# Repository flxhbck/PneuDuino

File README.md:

# PneuDuino

Pneuduino is a toolkit for controlling air flow and pressure to design robots that are soft, furniture that is adaptive, clothing that is intelligent, art pieces that are breathing, and many more things.

Disclaimer:
This toolkit is currently designed for workshops that we give. We are working on a more stable version for personal use. In the meantime, you are welcome to use what you find here - but be aware that is a work in progress.

For more information visit http://pneuduino.org/toolkit/

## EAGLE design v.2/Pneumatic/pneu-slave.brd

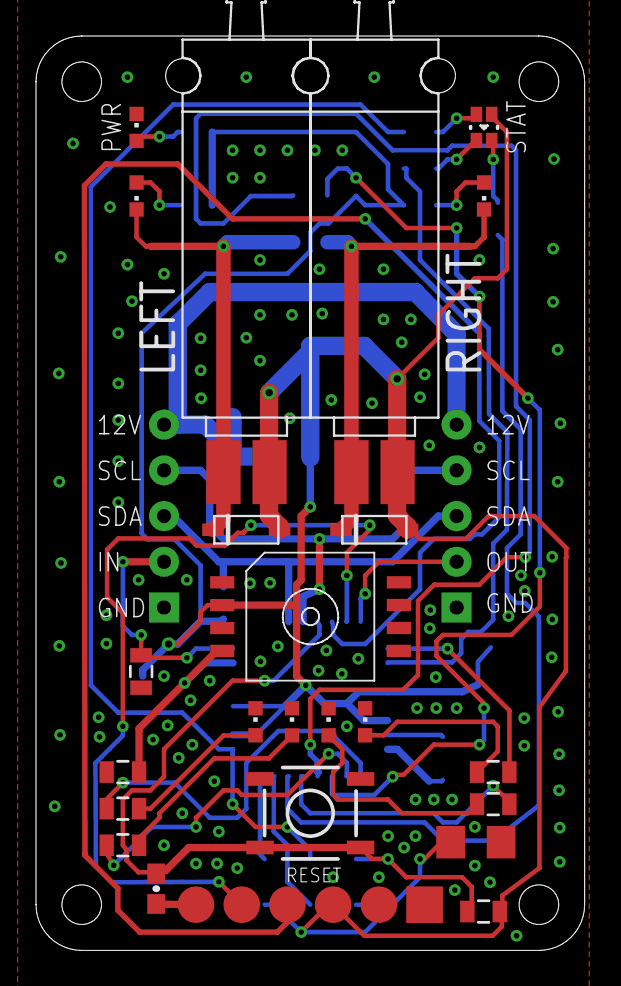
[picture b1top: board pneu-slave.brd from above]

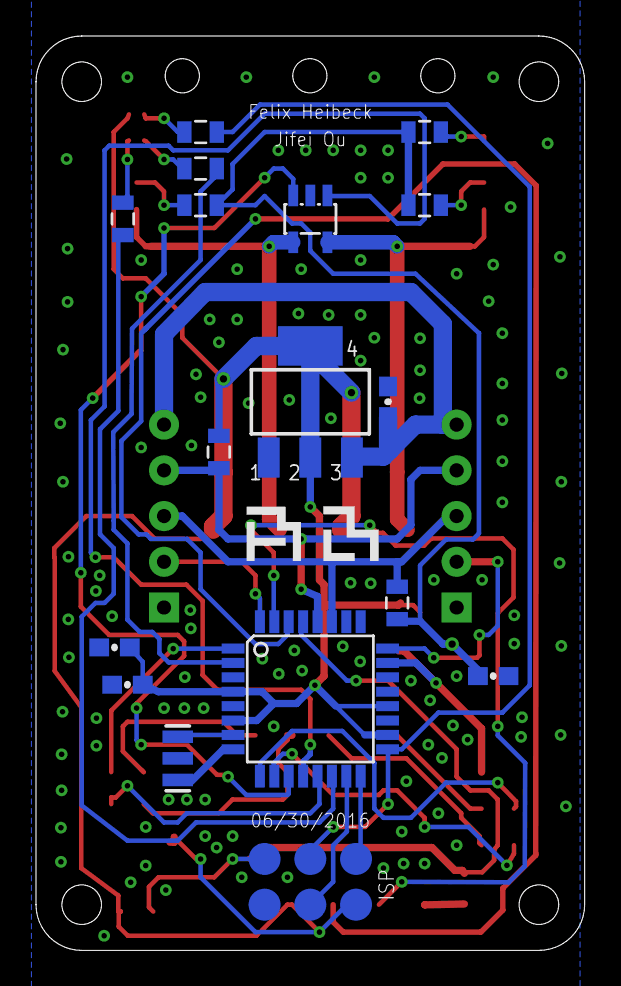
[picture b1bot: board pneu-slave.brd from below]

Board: 2 copper layers, 30.5 x 50.8 mm, 42 parts (17 on the bottom side), 37 nets.

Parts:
C1, C2, C5, C8, C10: 0.1uF; 0603-CAP
C4: 22uF; 1206
C7: 470pF; 0805
D1, D2: SOD-123
LED_PR1, LED_PR2, LED_PR3, LED_PR4: WHITE; CHIPLED_0603
LED_PWR: RED; CHIPLED_0603
LED_STATUS: LTST-C19FD1WT; LTST
LED_V1, LED_V2: WHITE; CHIPLED_0603
Q1: 16Mhz; RESONATOR-SMD
R1, R2, R4, R7, R8, R9, R10, R11, R12, R13: 1k; 0805
R3: 10K; 0805
R5, R6: 4.7k; 0805
R14: 10k; 0805
S1: TAC_SWITCHSMD; TACTILE-SWITCH-SMD
U0: ATMEGA328; TQFP32-08
U1: NCP1117-5; LINEAR_SOT223
U2: MPXHZ6400
U3: QS5K2; SOT23-5L
U$10: ISP_POGO; POGO_ISP
U$11: S070V-2VALVE; S070C-2
U$12: FTDI_POGO
U$23, U$24: 1X05; 1X05_TIGHT

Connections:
+5V: C2.1, C4.1, C8.1, C10.1, D1.C, D2.C, LED_STATUS.+, R2.2, R3.1, R5.1, R6.2, R8.2, R11.2, U0.4, U0.6, U0.18, U0.20, U1.2, U1.4, U2.2, U$10.2, U$11.1-2, U$11.2-2, U$12.4
A0/PRESSURE: C7.2, U0.23, U2.4
D2/OUT: U0.32, U$23.P$4
D3: R1.2, U0.1
D4: R9.2, U0.2
D5: R7.2, U0.9
D6: R4.2, U0.10
D7: U0.11, U3.3
D8: U0.12, U3.1
D9: R10.2, U0.13
D10: R12.2, U0.14
DTR: C5.2, U$12.1
GND: C1.2, C2.2, C4.2, C7.1, C8.2, C10.2, LED_PR1.C, LED_PR2.C, LED_PR3.C, LED_PR4.C, LED_PWR.C, Q1.2, R14.1, S1.1, S1.2, U0.3, U0.5, U0.21, U1.1, U2.3, U3.2, U$10.6, U$12.5, U$12.6, U$23.P$5, U$24.P$5
IN_PORT: R14.2, U0.24, U$24.P$4
M1_VGND: D1.A, LED_V2.C, U3.4, U$11.2-1
M2_VGND: D2.A, LED_V1.C, U3.5, U$11.1-1
MISO: U0.16, U$10.1
MOSI: U0.15, U$10.4
unnamed: LED_PR2.A, R4.1
unnamed: LED_PR1.A, R7.1
unnamed: Q1.1, U0.8
unnamed: LED_PR4.A, R1.1
unnamed: LED_V2.A, R2.1
unnamed: LED_V1.A, R8.1
unnamed: Q1.3, U0.7
unnamed: LED_PR3.A, R10.1
unnamed: LED_PWR.A, R11.1
unnamed: LED_STATUS.R, R9.1
unnamed: LED_STATUS.G, R12.1
unnamed: LED_STATUS.B, R13.1
RESET: C5.1, R3.2, S1.3, S1.4, U0.29, U$10.5
RX: U0.30, U$12.3
SCK: R13.2, U0.17, U$10.3
SCL: R6.1, U0.28, U$23.P$3, U$24.P$3
SDA: R5.2, U0.27, U$23.P$2, U$24.P$2
TX: U0.31, U$12.2
VIN: C1.1, U1.3, U$23.P$1, U$24.P$1

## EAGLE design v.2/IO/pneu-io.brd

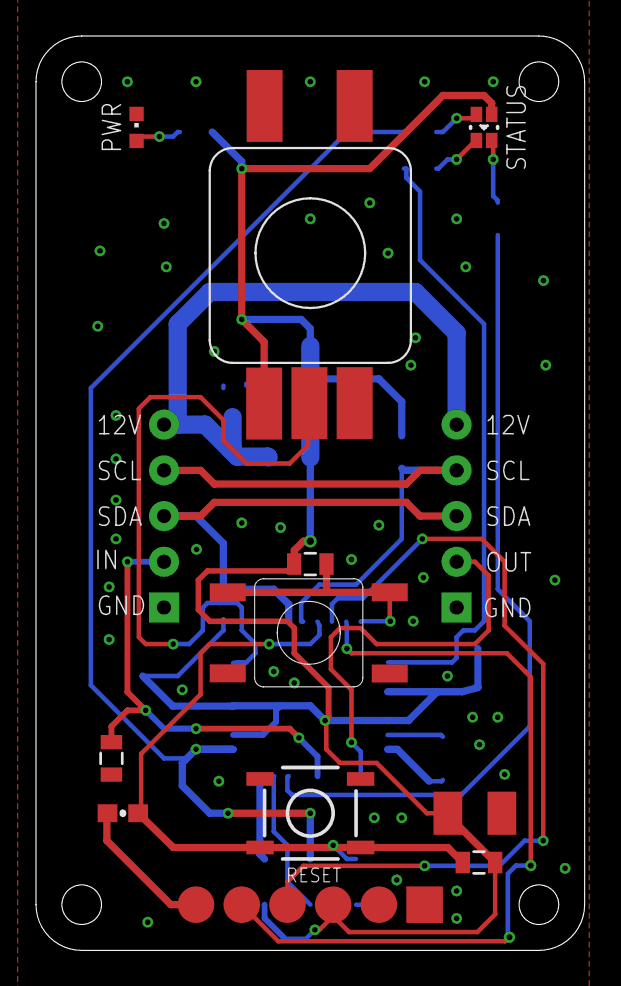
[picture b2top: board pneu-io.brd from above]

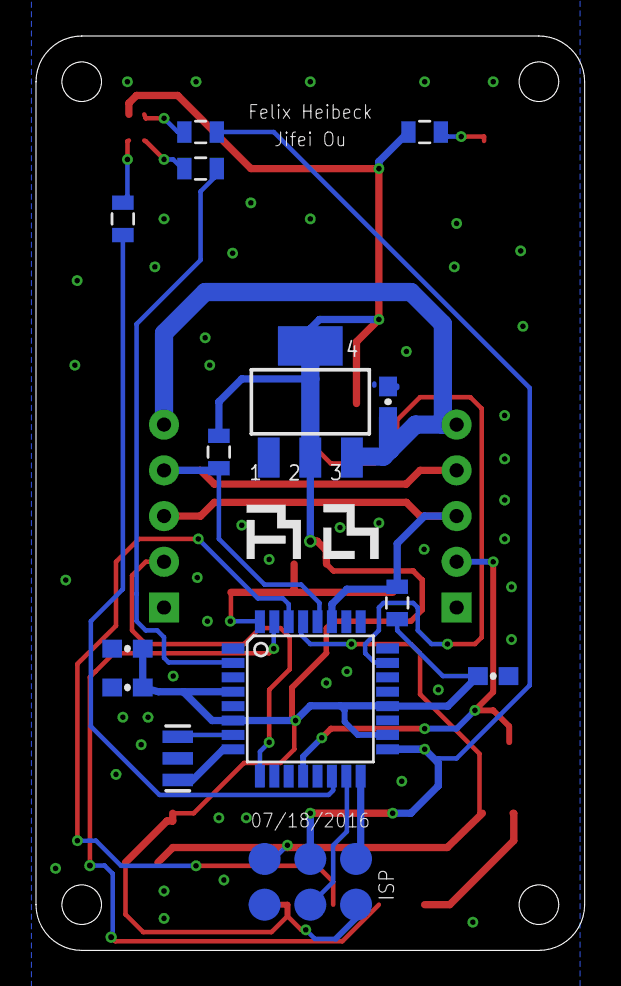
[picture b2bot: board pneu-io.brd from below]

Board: 2 copper layers, 30.5 x 50.8 mm, 27 parts (14 on the bottom side), 24 nets.

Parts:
C1, C2, C5, C8, C10: 0.1uF; 0603-CAP
C3: 22uF; SMC_B
IC3: ATMEGA328; TQFP32-08
PWR: CHIPLED_0603
Q1: 16Mhz; RESONATOR-SMD
R1, R3: 10K; 0805
R5, R6: 4.7k; 0805
R9, R11, R12, R13: 1k; 0805
R14: 10k; 0805
S1: TAC_SWITCHSMD; TACTILE-SWITCH-SMD
U2: NCP1117-5; LINEAR_SOT223
U$1: RS-014R05; SWITCH-11MM
U$2: PRS11S
U$10: ISP_POGO; POGO_ISP
U$12: FTDI_POGO
U$21: LTST-C19FD1WT; LTST
U$24, U$27: 1X05; 1X05_TIGHT

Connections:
+5V: C2.1, C3.+, C8.1, C10.1, IC3.4, IC3.6, IC3.18, IC3.20, R1.1, R3.1, R5.1, R6.2, R11.2, U2.2, U2.4, U$2.1, U$10.2, U$12.4, U$21.+
A0/POT: IC3.23, U$2.2
D2/BTN: IC3.32, R1.2, U$1.A, U$1.H
D4: IC3.2, R9.2
D5/OUT: IC3.9, U$27.P$4
D8: IC3.12, R14.2, U$24.P$4
D10: IC3.14, R12.2
DTR: C5.2, U$12.1
GND: C1.2, C2.2, C3.-, C8.2, C10.2, IC3.3, IC3.5, IC3.21, PWR.C, Q1.2, R14.1, S1.1, S1.2, U2.1, U$1.B, U$1.D, U$2.3, U$10.6, U$12.5, U$12.6, U$24.P$5, U$27.P$5
MISO: IC3.16, U$10.1
MOSI: IC3.15, U$10.4
unnamed: IC3.8, Q1.1
unnamed: IC3.7, Q1.3
unnamed: PWR.A, R11.1
unnamed: R9.1, U$21.R
unnamed: R12.1, U$21.G
unnamed: R13.1, U$21.B
RESET: C5.1, IC3.29, R3.2, S1.3, S1.4, U$10.5
RX: IC3.30, U$12.3
SCK: IC3.17, R13.2, U$10.3
SCL: IC3.28, R6.1, U$24.P$3, U$27.P$3
SDA: IC3.27, R5.2, U$24.P$2, U$27.P$2
TX: IC3.31, U$12.2
VIN: C1.1, U2.3, U$24.P$1, U$27.P$1

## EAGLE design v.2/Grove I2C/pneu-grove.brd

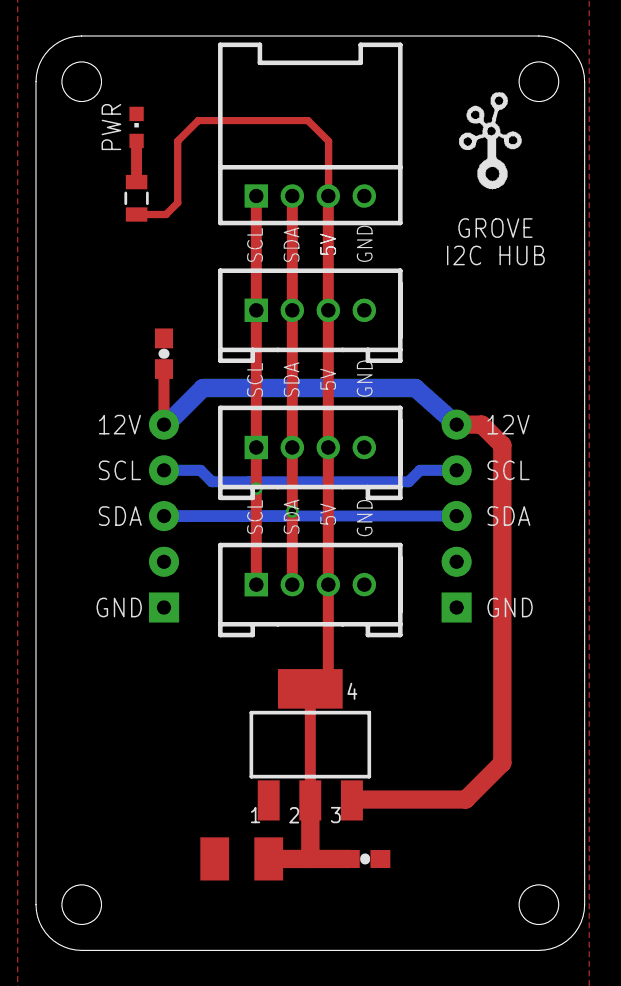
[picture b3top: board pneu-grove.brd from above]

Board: 2 copper layers, 30.5 x 50.8 mm, 13 parts (0 on the bottom side), 6 nets.

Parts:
C1, C2: 0.1uF; 0603-CAP
C3: 22uF; SMC_B
J1, J4, J5: TWIG-2.0-DIP; 2.0_1X4
J12: A3; 4P-2.0-90D
PWR: CHIPLED_0603
R11: 1k; 0805
U2: NCP1117-5; LINEAR_SOT223
U$1: TWIGLOGOTWIGLOGO_SMALL; TWIGLOGO_SMALL
U$23, U$24: 1X05; 1X05_TIGHT

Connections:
+5V: C2.1, C3.+, J1.3, J4.3, J5.3, J12.3, R11.2, U2.2, U2.4
GND: C1.2, C2.2, C3.-, J1.4, J4.4, J5.4, J12.4, PWR.C, U2.1, U$23.P$5, U$24.P$5
unnamed: PWR.A, R11.1
SCL: J1.1, J4.1, J5.1, J12.1, U$23.P$3, U$24.P$3
SDA: J1.2, J4.2, J5.2, J12.2, U$23.P$2, U$24.P$2
VIN: C1.1, U2.3, U$23.P$1, U$24.P$1

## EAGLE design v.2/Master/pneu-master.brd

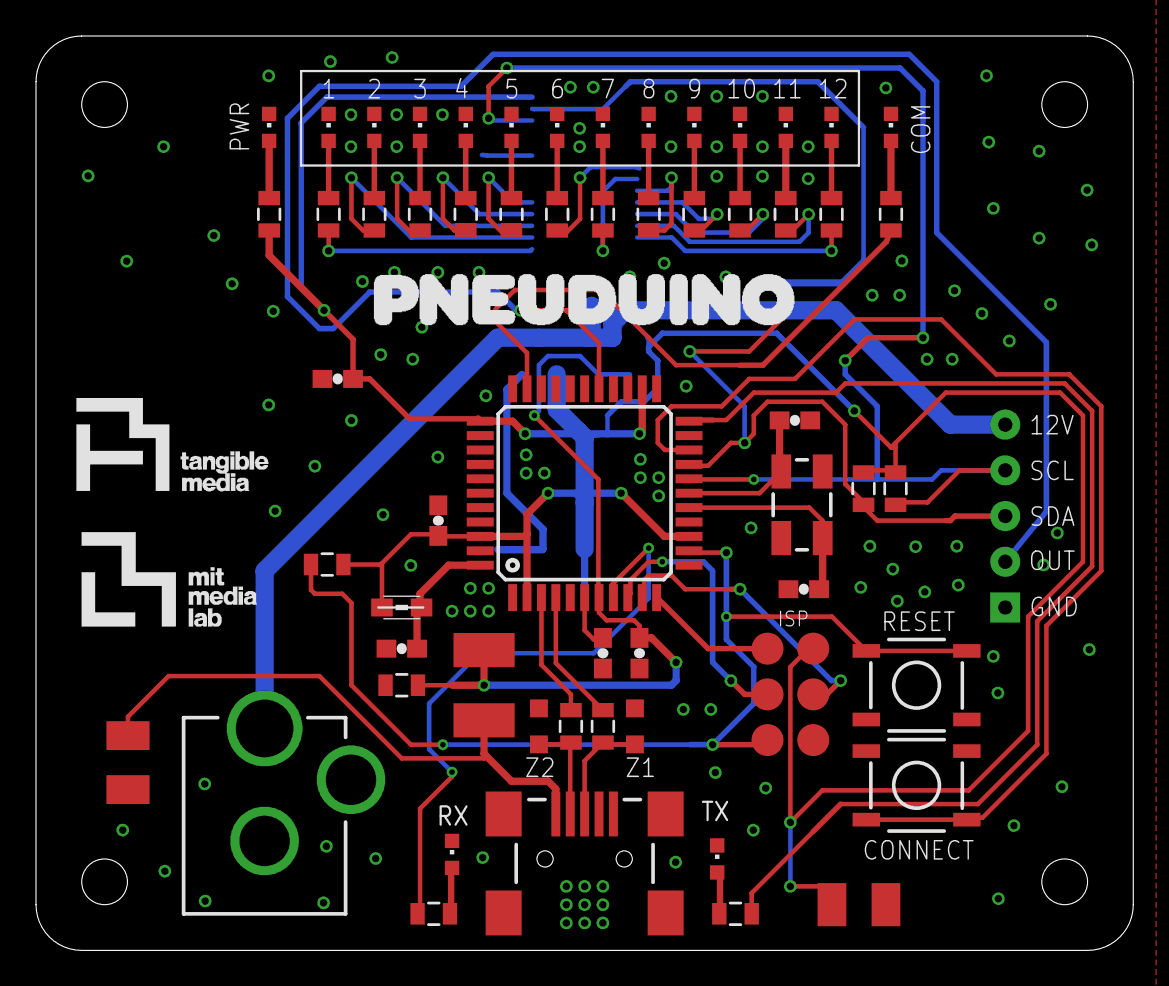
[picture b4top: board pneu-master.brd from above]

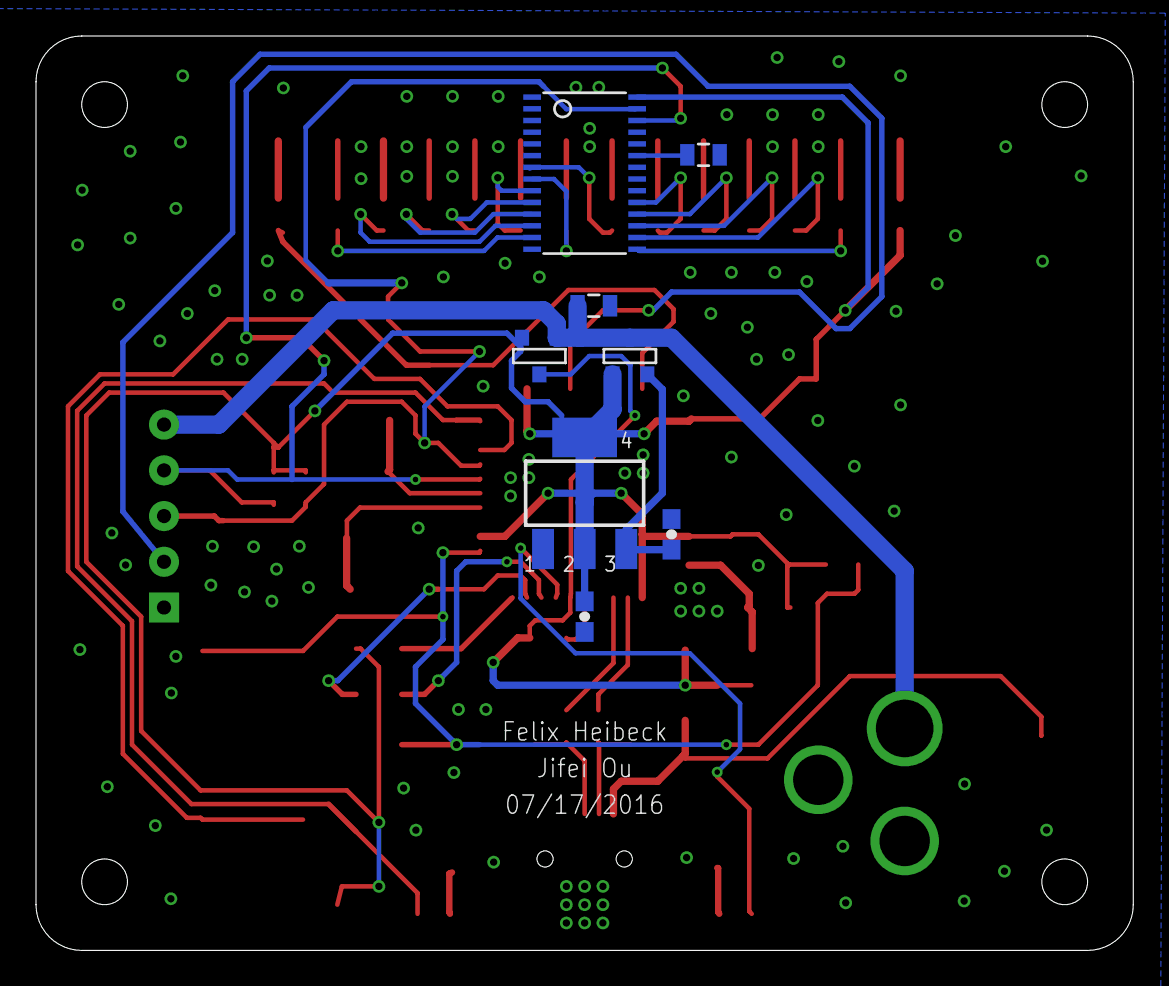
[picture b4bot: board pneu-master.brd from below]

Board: 2 copper layers, 61.0 x 50.8 mm, 67 parts (8 on the bottom side), 54 nets.

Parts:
1, 2, 3, 4, 5, 6, 7, 8, 9, 10, 11, 12: CHIPLED_0603
C1, C2, C6, C8, C10: 0.1uF; 0603-CAP
C3, C14: 22uF; SMC_B
C4, C7: 1uF; 0603-CAP
C16, C17: 22pF; 0603-CAP
CN1: DCJACK_2MM_PTH
COM: CHIPLED_0603
F1: MF-MSMF050-2 500mA; L1812
L1: MH2029-300Y; 0805
PWR: CHIPLED_0603
R1, R4: 22; 0805
R2, R3, R9, R12: 10K; 0805
R5, R6: opt; 0805
R10, R11, R13, R14, R15, R16, R17, R18, R19, R20, R21, R22, R23, R24, R25, R26: 1k; 0805
RX: CHIPLED_0603
S1, S2: TAC_SWITCHSMD; TACTILE-SWITCH-SMD
T1: FDN340P/PMV48XP; SOT-23
T2: PMV48XP; SOT-23
TX: CHIPLED_0603
U1: TSSOP28
U2: NCP1117-5; LINEAR_SOT223
U$3: USB-MINIB-5PIN; USB-MINIB
U$4: ATMEGA32U4-AU; TQFP44
U$10: ISP_POGO; POGO_ISP
U$14: 1X05; 1X05_TIGHT
Y2: 16MHz; CRYSTAL-SMD-5X3
Z1, Z2: CG0603MLC-05E; CT/CN0603

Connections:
+5V: C2.1, C3.+, C8.1, C10.1, L1.1, R3.1, R5.1, R6.2, R11.2, T1.2, T2.3, U1.28, U2.2, U2.4, U$4.2, U$4.14, U$4.24, U$4.34, U$4.42, U$10.2
+VIN: C1.1, T2.2, U2.3
BTN: S2.1, S2.2, U$4.20
D13: R10.2, U$4.32
D+: R4.1, U$3.D+, Z1.1
D-: R1.1, U$3.D-, Z2.1
DATA_OUT: U$4.27, U$14.P$4
GND: 1.C, 2.C, 3.C, 4.C, 5.C, 6.C, 7.C, 8.C, 9.C, 10.C, 11.C, 12.C, C1.2, C2.2, C3.-, C4.1, C6.2, C7.2, C8.2, C10.2, C14.-, C16.2, C17.2, CN1.GND, COM.C, PWR.C, R2.1, R9.1, R12.2, RX.C, S1.1, S1.2, S2.3, S2.4, TX.C, U1.1, U1.2, U1.3, U1.4, U1.5, U1.14, U1.24, U1.25, U2.1, U$3.GND, U$3.MTN1, U$3.MTN2, U$3.MTN3, U$3.MTN4, U$4.5, U$4.15, U$4.23, U$4.33, U$4.35, U$4.43, U$10.6, U$14.P$5, Z1.2, Z2.2
LED1: R13.2, U1.15
LED2: R14.2, U1.16
LED3: R15.2, U1.17
LED4: R16.2, U1.18
LED5: R17.2, U1.19
LED6: R18.2, U1.7
LED7: R19.2, U1.8
LED8: R20.2, U1.9
LED9: R21.2, U1.10
LED10: R22.2, U1.11
LED11: R25.2, U1.12
LED12: R26.2, U1.13
MISO: U$4.11, U$10.1
MOSI: U$4.10, U$10.4
unnamed: C16.1, U$4.17, Y2.3
unnamed: C17.1, U$4.16, Y2.1
unnamed: C7.1, U$4.6
unnamed: C4.2, L1.2, U$4.44
unnamed: R23.1, RX.A
unnamed: R24.1, TX.A
unnamed: COM.A, R10.1
unnamed: PWR.A, R11.1
unnamed: R12.1, U1.23
unnamed: 1.A, R13.1
unnamed: 2.A, R14.1
unnamed: 3.A, R15.1
unnamed: 4.A, R16.1
unnamed: 5.A, R17.1
unnamed: 6.A, R18.1
unnamed: 7.A, R19.1
unnamed: 8.A, R20.1
unnamed: 9.A, R21.1
unnamed: 10.A, R22.1
unnamed: 11.A, R25.1
unnamed: 12.A, R26.1
RD+: R4.2, U$4.4
RD-: R1.2, U$4.3
RESET: R3.2, S1.3, S1.4, U$4.13, U$10.5
RXLED: R23.2, U$4.8
SCK: U$4.9, U$10.3
SCL: R6.1, U1.26, U$4.18, U$14.P$3
SDA: R5.2, U1.27, U$4.19, U$14.P$2
TXLED: R24.2, U$4.22
VIN: CN1.PWR, R9.2, T1.3, T2.1, U$14.P$1
VUSB: C6.1, F1.2, R2.2, T1.1, U$4.7
VUSBD: C14.+, F1.1, U$3.VBUS

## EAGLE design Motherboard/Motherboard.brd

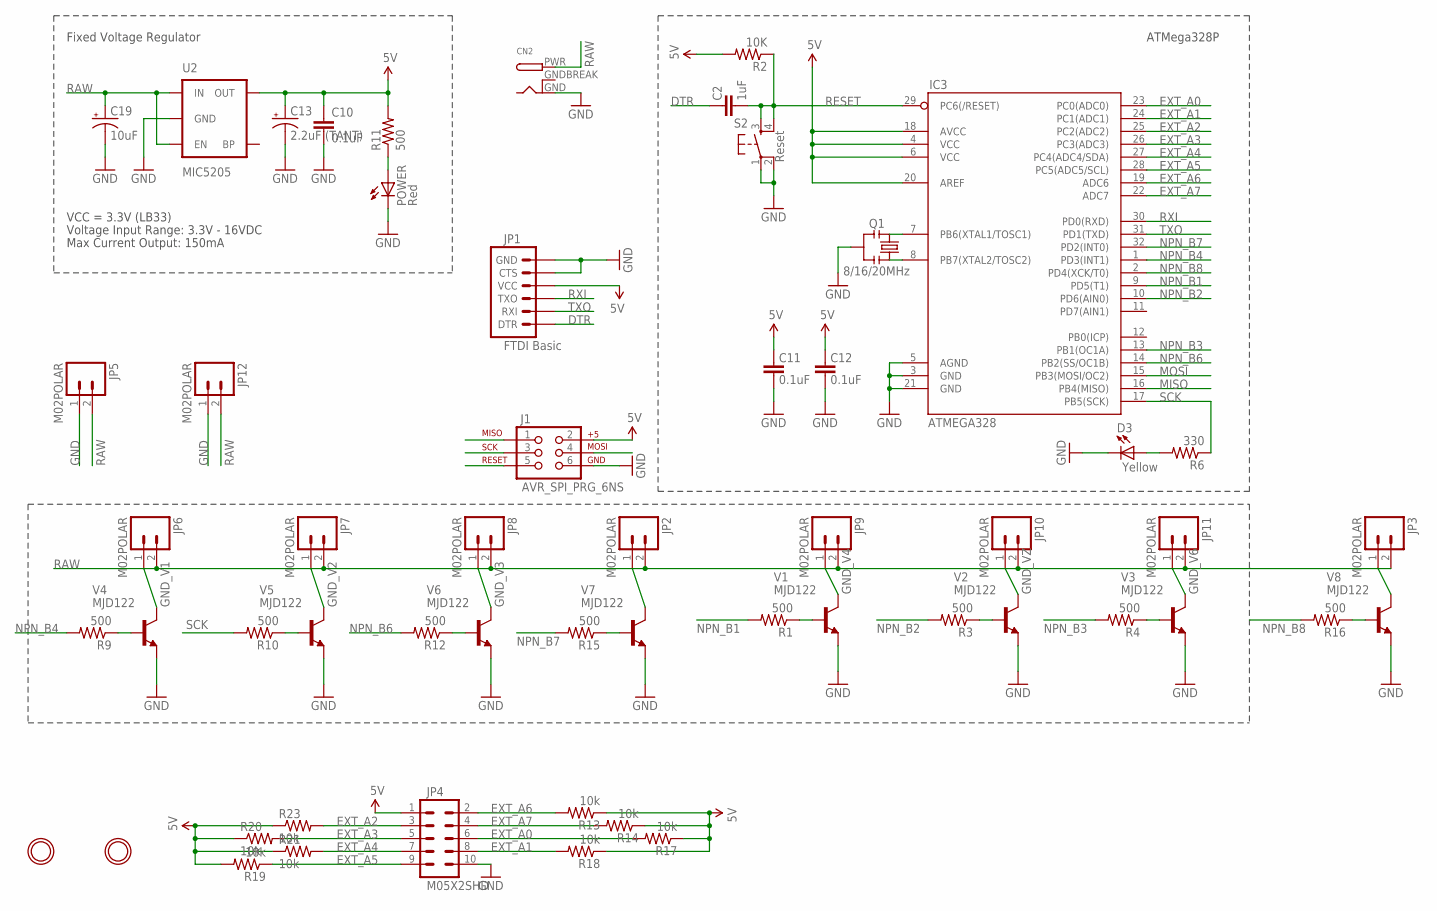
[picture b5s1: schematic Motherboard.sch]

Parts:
C2: 1uF; 0805
C10, C11, C12: 0.1uF; 0805
C13: 2.2uF (TANT); EIA3216
C19: 10uF; EIA3216
CN2: DCBARRELPTH; DCJACK_2MM_PTH
D3: Yellow; LED-1206
IC3: ATMEGA328; TQFP32-08
J1: AVR_SPI_PRG_6NS; 2X3-NS
JP1: FTDI Basic; 1X06
JP2, JP3, JP5, JP6, JP7, JP8, JP9, JP10, JP11, JP12: M02POLAR; MOLEX-1X2
JP4: M05X2SHD; 2X5-SHROUDED
POWER: Red; LED-1206
Q1: 8/16/20MHz; RESONATOR-SMD
R1, R3, R4, R9, R10, R11, R12, R15, R16: 500; 0805
R2: 10K; 0805
R6: 330; 0805
R13, R14, R17, R18, R19, R20, R21, R23: 10k; 0805
S2: Reset; TACTILE_SWITCH_SMD
U2: MIC5205; SOT23-5
U$1, U$2: MOUNTINGHOLE2.5; MOUNTINGHOLE_2.5_PLATED
V1, V2, V3, V4, V5, V6, V7, V8: MJD122; DPAK

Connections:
5V: C10.1, C11.2, C12.2, C13.A (+), IC3.4 (VCC), IC3.6 (VCC), IC3.18 (AVCC), IC3.20 (AREF), J1.2, JP1.4 (VCC), JP4.1, R2.2, R11.2, R13.1, R14.1, R17.1, R18.1, R19.2, R20.1, R21.1, R23.1, U2.5 (OUT)
DTR: C2.2, JP1.1 (DTR)
EXT_A0: IC3.23 (PC0(ADC0)), JP4.6, R17.2
EXT_A1: IC3.24 (PC1(ADC1)), JP4.8, R18.2
EXT_A2: IC3.25 (PC2(ADC2)), JP4.3, R23.2
EXT_A3: IC3.26 (PC3(ADC3)), JP4.5, R20.2
EXT_A4: IC3.27 (PC4(ADC4/SDA)), JP4.7, R21.2
EXT_A5: IC3.28 (PC5(ADC5/SCL)), JP4.9, R19.1
EXT_A6: IC3.19 (ADC6), JP4.2, R13.2
EXT_A7: IC3.22 (ADC7), JP4.4, R14.2
GND: C10.2, C11.1, C12.1, C13.C (-), C19.C (-), CN2.GND, D3.C, IC3.3 (GND), IC3.5 (AGND), IC3.21 (GND), J1.6, JP1.5 (CTS), JP1.6 (GND), JP4.10, JP5.1, JP12.1, POWER.C, Q1.2, S2.1, S2.2, U2.2 (GND), V1.3 (E), V2.3 (E), V3.3 (E), V4.3 (E), V5.3 (E), V6.3 (E), V7.3 (E), V8.3 (E)
GNDBREAK: CN2.GNDBREAK
GND_V1: JP6.1, V4.4 (C)
GND_V2: JP7.1, V5.4 (C)
GND_V3: JP8.1, V6.4 (C)
GND_V4: JP9.1, V1.4 (C)
GND_V6: JP11.1, V3.4 (C)
GND_V7: JP2.1, V7.4 (C)
GND_V8: JP3.1, V8.4 (C)
GND_VZ: JP10.1, V2.4 (C)
MISO: IC3.16 (PB4(MISO)), J1.1
MOSI: IC3.15 (PB3(MOSI/OC2)), J1.4
unnamed: IC3.8 (PB7(XTAL2/TOSC2)), Q1.1
unnamed: IC3.7 (PB6(XTAL1/TOSC1)), Q1.3
unnamed: R9.1, V4.1 (B)
unnamed: R1.1, V1.1 (B)
unnamed: R10.1, V5.1 (B)
unnamed: R12.1, V6.1 (B)
unnamed: D3.A, R6.2
unnamed: R3.1, V2.1 (B)
unnamed: R4.1, V3.1 (B)
unnamed: R16.1, V8.1 (B)
unnamed: R15.1, V7.1 (B)
unnamed: POWER.A, R11.1
NPN_B1: IC3.9 (PD5(T1)), R1.2
NPN_B2: IC3.10 (PD6(AIN0)), R3.2
NPN_B3: IC3.13 (PB1(OC1A)), R4.2
NPN_B4: IC3.1 (PD3(INT1)), R9.2
NPN_B6: IC3.14 (PB2(SS/OC1B)), R12.2
NPN_B7: IC3.32 (PD2(INT0)), R15.2
NPN_B8: IC3.2 (PD4(XCK/T0)), R16.2
RAW: C19.A (+), CN2.PWR, JP2.2, JP3.2, JP5.2, JP6.2, JP7.2, JP8.2, JP9.2, JP10.2, JP11.2, JP12.2, U2.1 (IN), U2.3 (EN)
RESET: C2.1, IC3.29 (PC6(/RESET)), J1.5, R2.1, S2.3, S2.4
RXI: IC3.30 (PD0(RXD)), JP1.3 (TXO)
SCK: IC3.17 (PB5(SCK)), J1.3, R6.1, R10.2
TXO: IC3.31 (PD1(TXD)), JP1.2 (RXI)

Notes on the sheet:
Max Current Output: 150mA
VCC = 3.3V (LB33)
Voltage Input Range: 3.3V - 16VDC
Fixed Voltage Regulator
ATMega328P

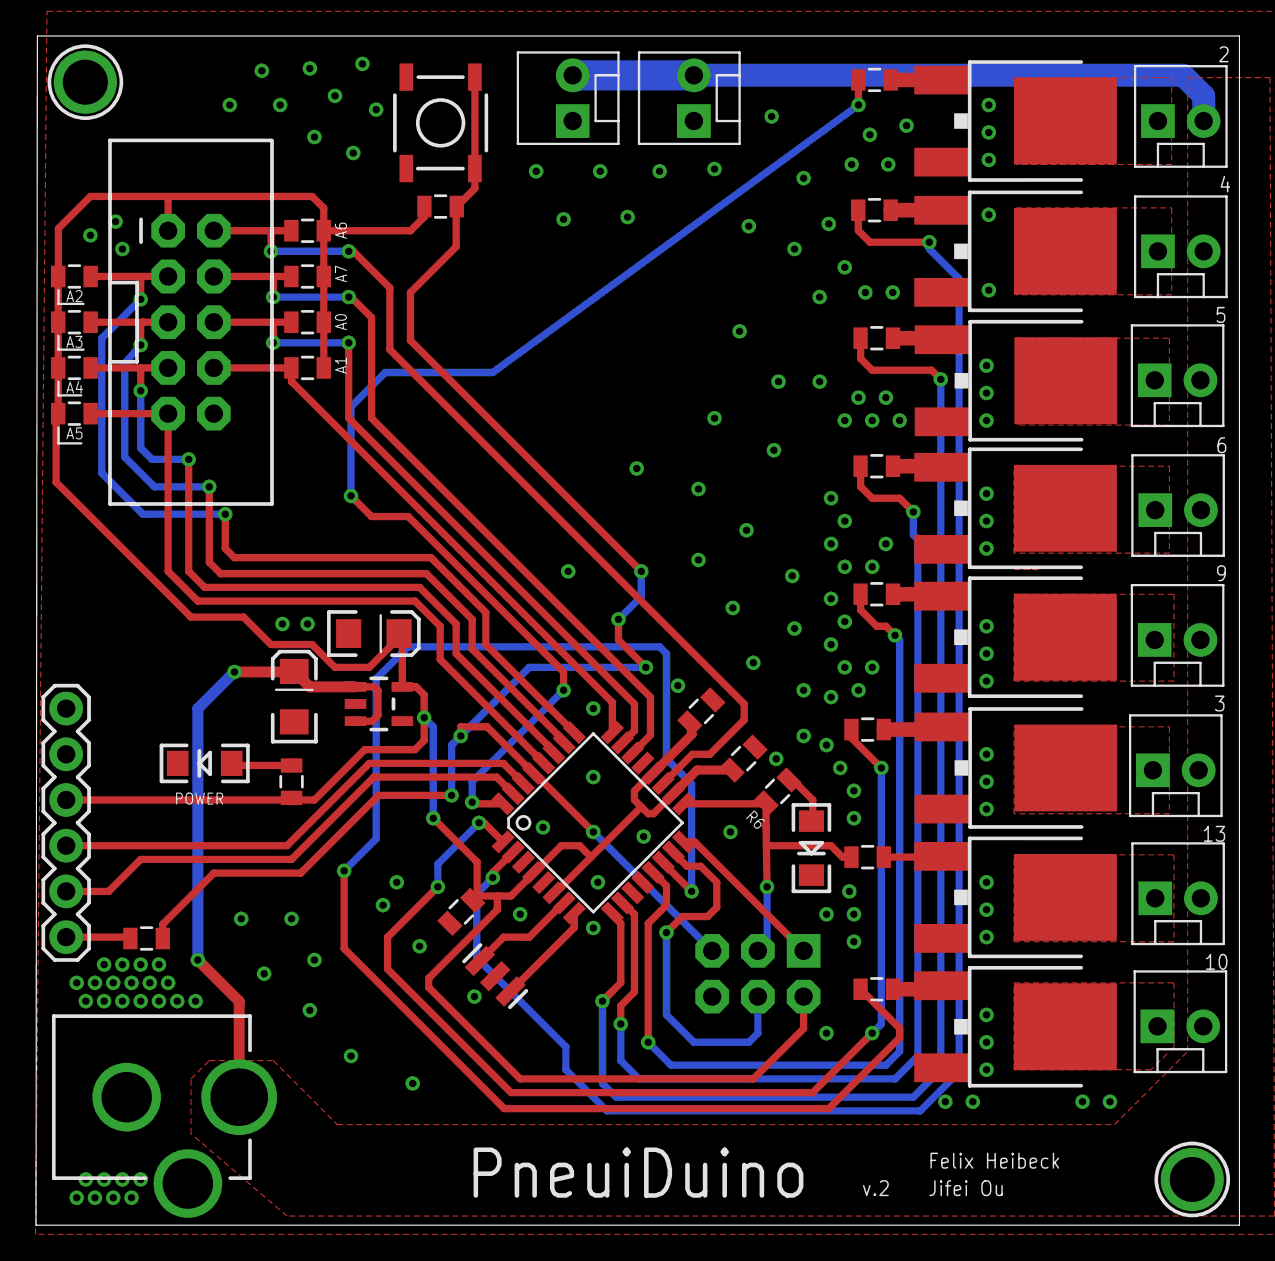
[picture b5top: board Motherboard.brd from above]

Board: 2 copper layers, 66.9 x 66.1 mm, 55 parts (0 on the bottom side), 45 nets.

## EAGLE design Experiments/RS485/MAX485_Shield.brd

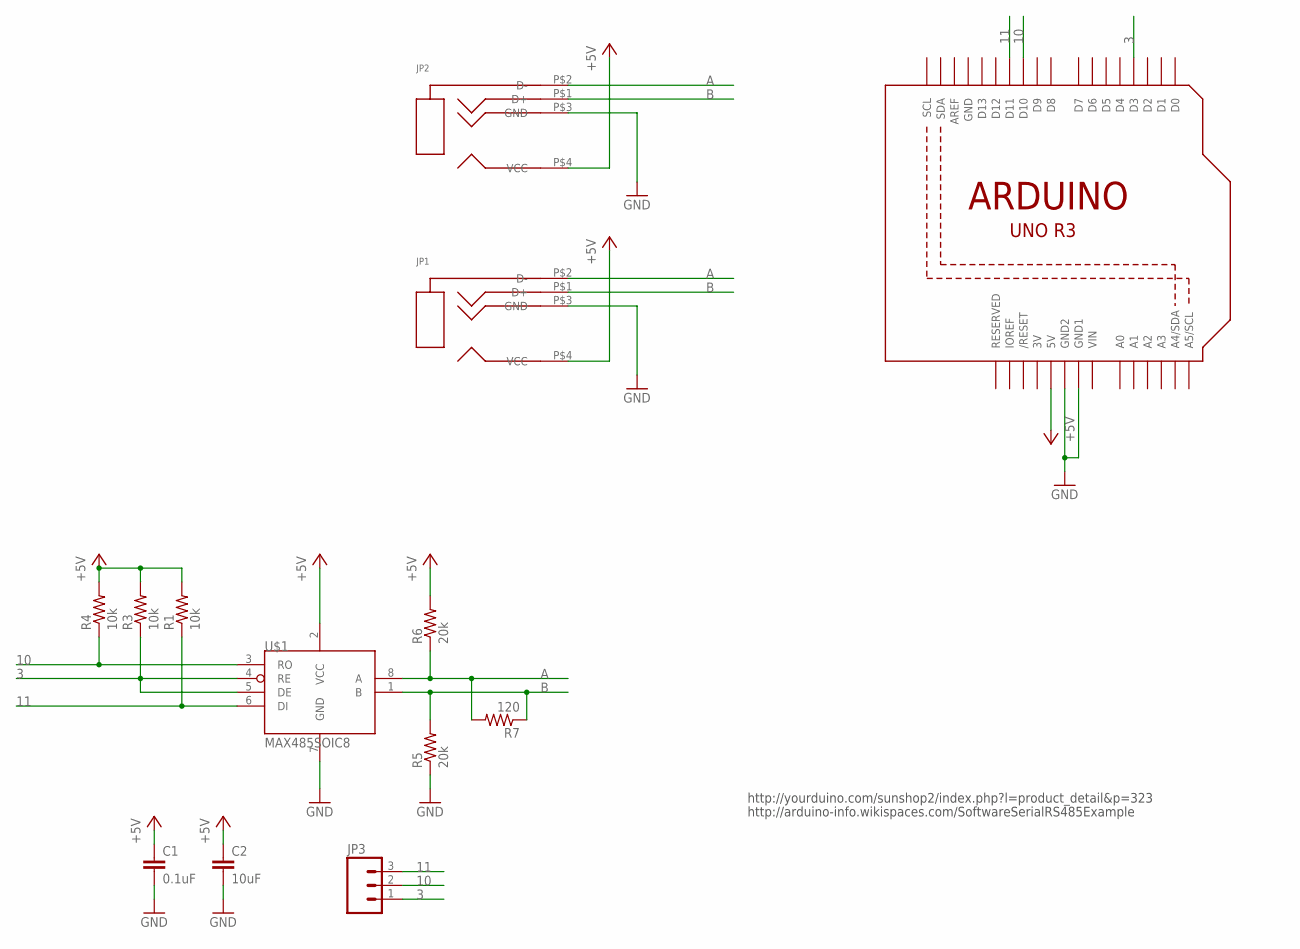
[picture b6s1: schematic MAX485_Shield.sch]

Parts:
C1: 0.1uF; 0805
C2: 10uF; 0805
JP1, JP2: AUDIOJACK-4CONTACTS; SJ-4351X-SMT
JP3: M03PTH; 1X03
R1, R3, R4: 10k; 0805
R5, R6: 20k; 0805
R7: 120; 0805
U1: ARDUINOR3-BPLACE
U$1: MAX485SOIC8; SOIC8

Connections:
3: JP3.1, R3.1, U1.D3, U$1.4 (RE), U$1.5 (DE)
3V: U1.3V
10: JP3.2, R4.1, U1.D10, U$1.3 (RO)
11: JP3.3, R1.1, U1.D11, U$1.6 (DI)
+5V: C1.1, C2.1, JP1.P$4 (VCC), JP2.P$4 (VCC), R1.2, R3.2, R4.2, R6.2, U1.5V, U$1.2 (VCC)
A: JP1.P$2 (D-), JP2.P$2 (D-), R6.1, R7.2, U$1.8 (A)
B: JP1.P$1 (D+), JP2.P$1 (D+), R5.2, R7.1, U$1.1 (B)
GND: C1.2, C2.2, JP1.P$3 (GND), JP2.P$3 (GND), R5.1, U1.GND, U1.GND1, U1.GND2, U$1.7 (GND)
VIN: U1.VIN

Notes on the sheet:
http://yourduino.com/sunshop2/index.php?l=product_detail&p=323
http://arduino-info.wikispaces.com/SoftwareSerialRS485Example

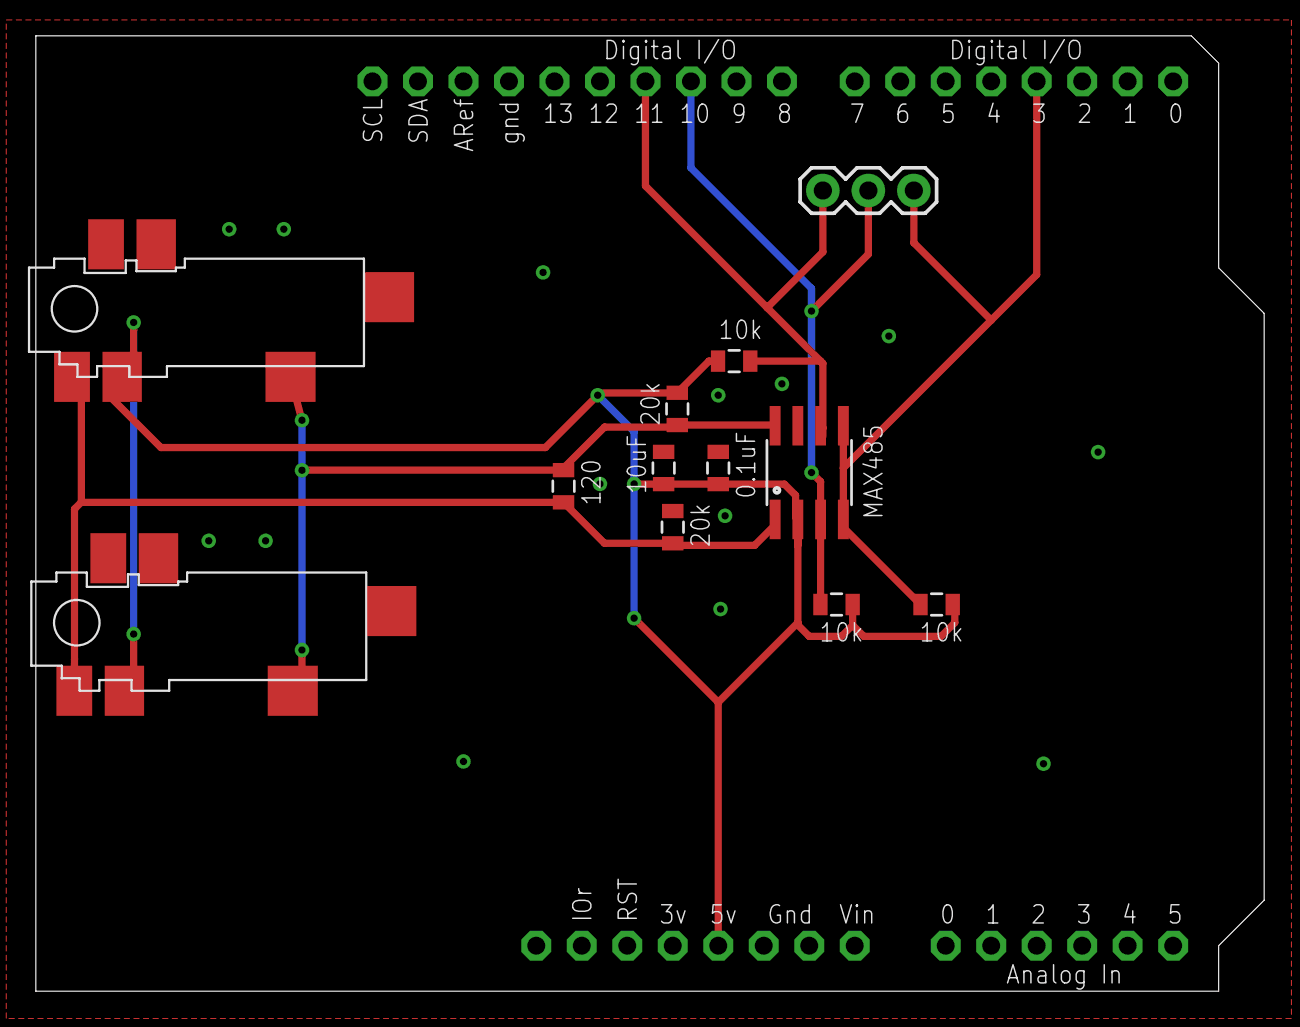
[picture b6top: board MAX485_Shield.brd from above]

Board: 2 copper layers, 68.6 x 53.3 mm, 13 parts (0 on the bottom side), 7 nets.

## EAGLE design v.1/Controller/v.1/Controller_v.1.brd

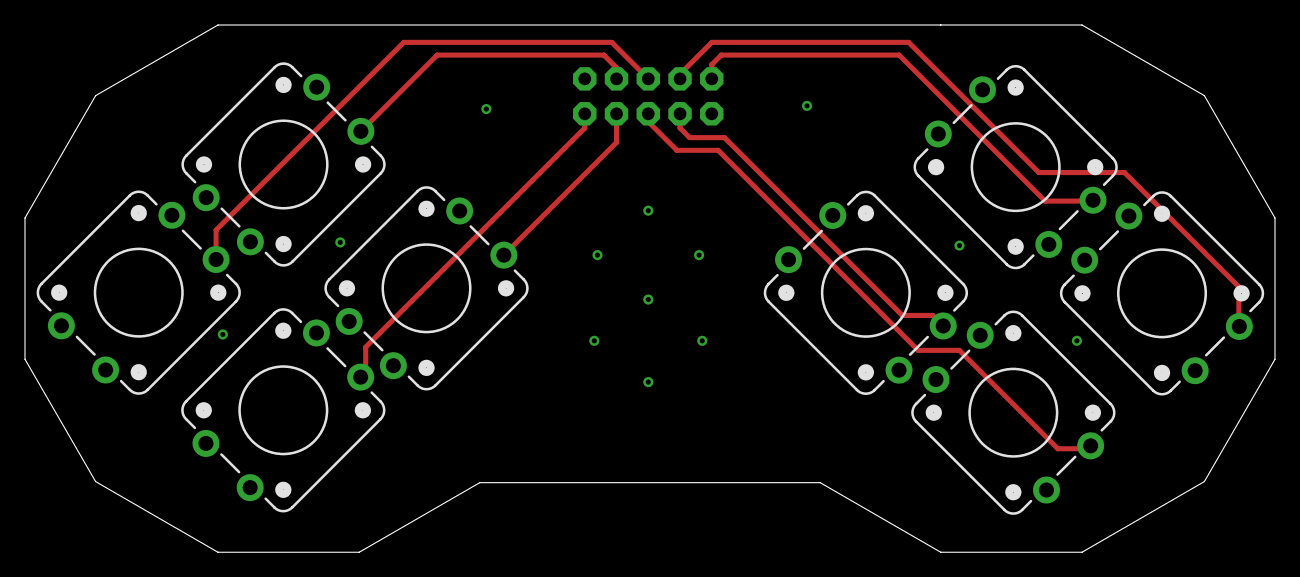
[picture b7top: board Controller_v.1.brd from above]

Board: 2 copper layers, 100.0 x 42.2 mm, 9 parts (1 on the bottom side), 9 nets.

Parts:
JP1: M05X2SHD_LOCK; 2X5-SHROUDED_LOCK
S1, S2, S3, S5, S6, S7, S8, S9: SWITCH-MOMENTARY-212MM; TACTILE-PTH-12MM

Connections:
1: JP1.3, S9.1
2: JP1.5, S2.1
3: JP1.7, S7.3
4: JP1.9, S5.3
5: JP1.2, S1.1
6: JP1.4, S3.1
7: JP1.6, S8.3
8: JP1.8, S6.3
GND: JP1.1, JP1.10, S1.3, S2.3, S3.3, S5.1, S6.1, S7.1, S8.1, S9.3

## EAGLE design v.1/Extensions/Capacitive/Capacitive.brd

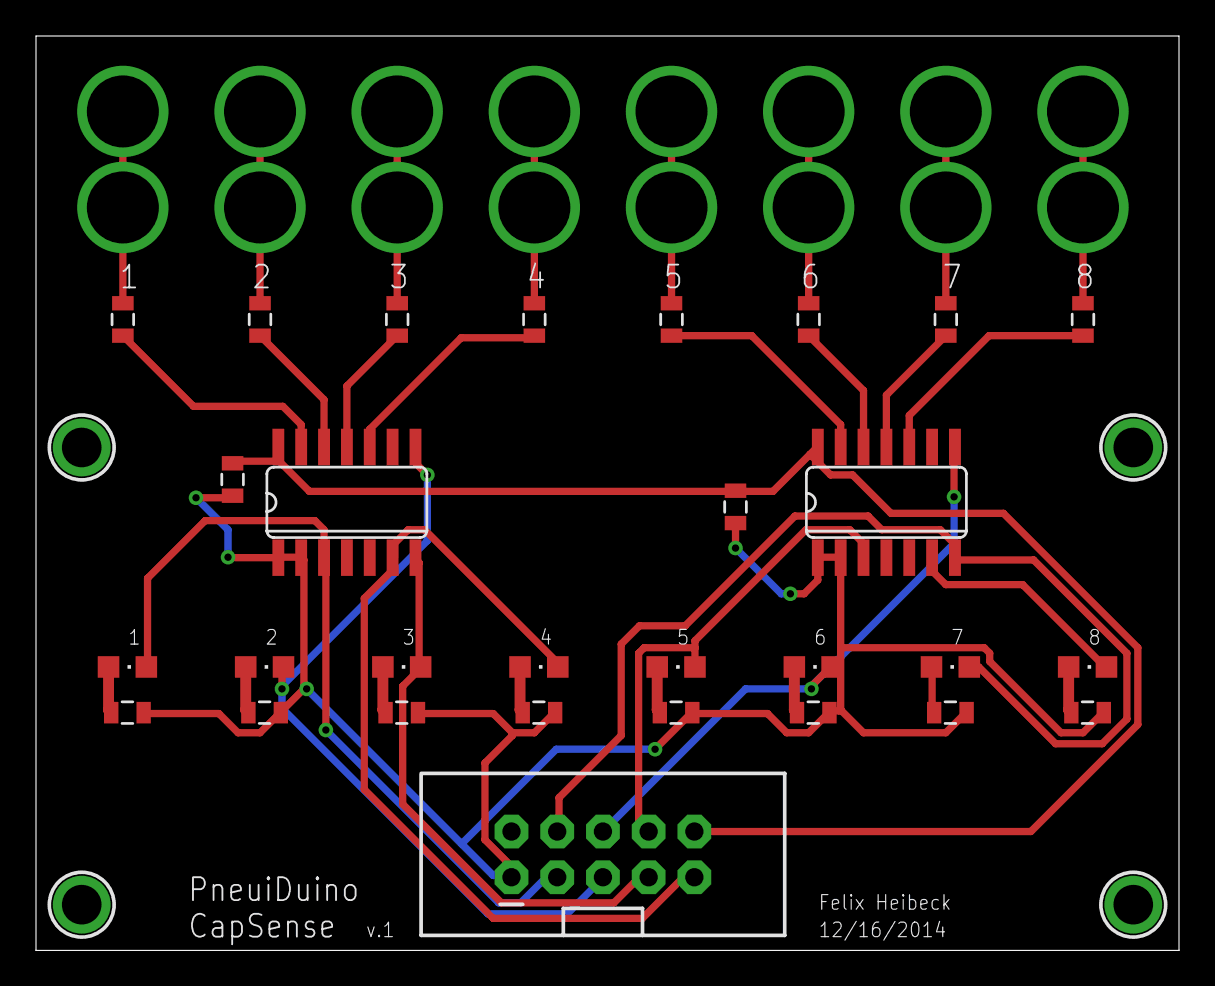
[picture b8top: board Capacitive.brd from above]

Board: 2 copper layers, 63.5 x 50.8 mm, 41 parts (0 on the bottom side), 34 nets.

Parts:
1, 2, 3, 4, 5, 6, 7, 8: CHIPLED_0805
C1, C2: 0.1uF; 0805
IC1, IC2: AT42QT1070; SO14
JP4: M05X2SHD; 2X5-SHROUDED
R1, R2, R3, R4, R5, R6, R7, R8: 470; 0805
R9, R10, R11, R12, R13, R14, R15, R16: 10k; 0805
U$1, U$2, U$3, U$4, U$5, U$6, U$7, U$8: ALLIGATOR_CONN; 3MM_ALLIGATOR
U$9, U$10, U$11, U$12: MOUNTINGHOLE2.0; MOUNTINGHOLE_2.0_PLATED

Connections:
5V: C1.1, C2.1, IC1.1, IC1.2, IC2.1, IC2.2, JP4.1, R1.1, R2.1, R3.1, R4.1, R5.1, R6.1, R7.1, R8.1
GND: C1.2, C2.2, IC1.14, IC2.14, JP4.10
unnamed: 1.A, R1.2
unnamed: 3.A, R2.2
unnamed: 2.A, R3.2
unnamed: 4.A, R4.2
unnamed: 8.A, R5.2
unnamed: 7.A, R6.2
unnamed: 6.A, R7.2
unnamed: 5.A, R8.2
unnamed: IC1.13, R9.2
unnamed: IC1.12, R10.2
unnamed: IC1.11, R11.2
unnamed: IC1.10, R12.2
unnamed: R12.1, U$4.ALLIGATOR, U$4.ALLIGATOR1
unnamed: R11.1, U$3.ALLIGATOR, U$3.ALLIGATOR1
unnamed: R10.1, U$2.ALLIGATOR, U$2.ALLIGATOR1
unnamed: R9.1, U$1.ALLIGATOR, U$1.ALLIGATOR1
unnamed: IC2.13, R13.2
unnamed: IC2.12, R14.2
unnamed: IC2.11, R15.2
unnamed: IC2.10, R16.2
unnamed: R14.1, U$6.ALLIGATOR, U$6.ALLIGATOR1
unnamed: R15.1, U$7.ALLIGATOR, U$7.ALLIGATOR1
unnamed: R16.1, U$8.ALLIGATOR, U$8.ALLIGATOR1
unnamed: R13.1, U$5.ALLIGATOR, U$5.ALLIGATOR1
O0: 1.C, IC1.3, JP4.3
O1: 2.C, IC1.8, JP4.5
O2: 3.C, IC1.7, JP4.7
O3: 4.C, IC1.6, JP4.9
O4: 5.C, IC2.3, JP4.8
O5: 6.C, IC2.8, JP4.6
O6: 7.C, IC2.7, JP4.4
O7: 8.C, IC2.6

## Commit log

2015-02-18 create
2015-09-26 added arduino library
    sans IO board part.
2015-09-26 -readme
2015-09-27 connect/reset on button press.
2015-09-27 +serial control example
    also edited the documentation
2015-09-27 edited the documentation header.
2015-10-10 added IO board. fixed address space.
2015-10-13 fixed checkNode problem
2016-02-29 minor changes.
2016-06-28 added 5th pin
    5th pin will allow dynamic addressing of the connected boards.
    also added holes in the corners for fixtures.
2016-07-13 added dxf
2016-07-13 proper naming
2016-07-13 .gitignore
2016-07-20 minor changes
    getting ready for production:
    correct indicator led position on master board
    add corner drills to slave boards
    generate silk screens
    adjust edge connector distance for better fit
2016-08-22 small updates..
2016-09-06 fixed byte problem in readPressure

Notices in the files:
parts and their libraries:
SparkFun-Resistors: Licensing: Creative Commons ShareAlike 4.0 International - https://creativecommons.org/licenses/by-sa/4.0
SparkFun-Capacitors: Licensing: CC v3.0 Share-Alike You are welcome to use this library for commercial purposes.
